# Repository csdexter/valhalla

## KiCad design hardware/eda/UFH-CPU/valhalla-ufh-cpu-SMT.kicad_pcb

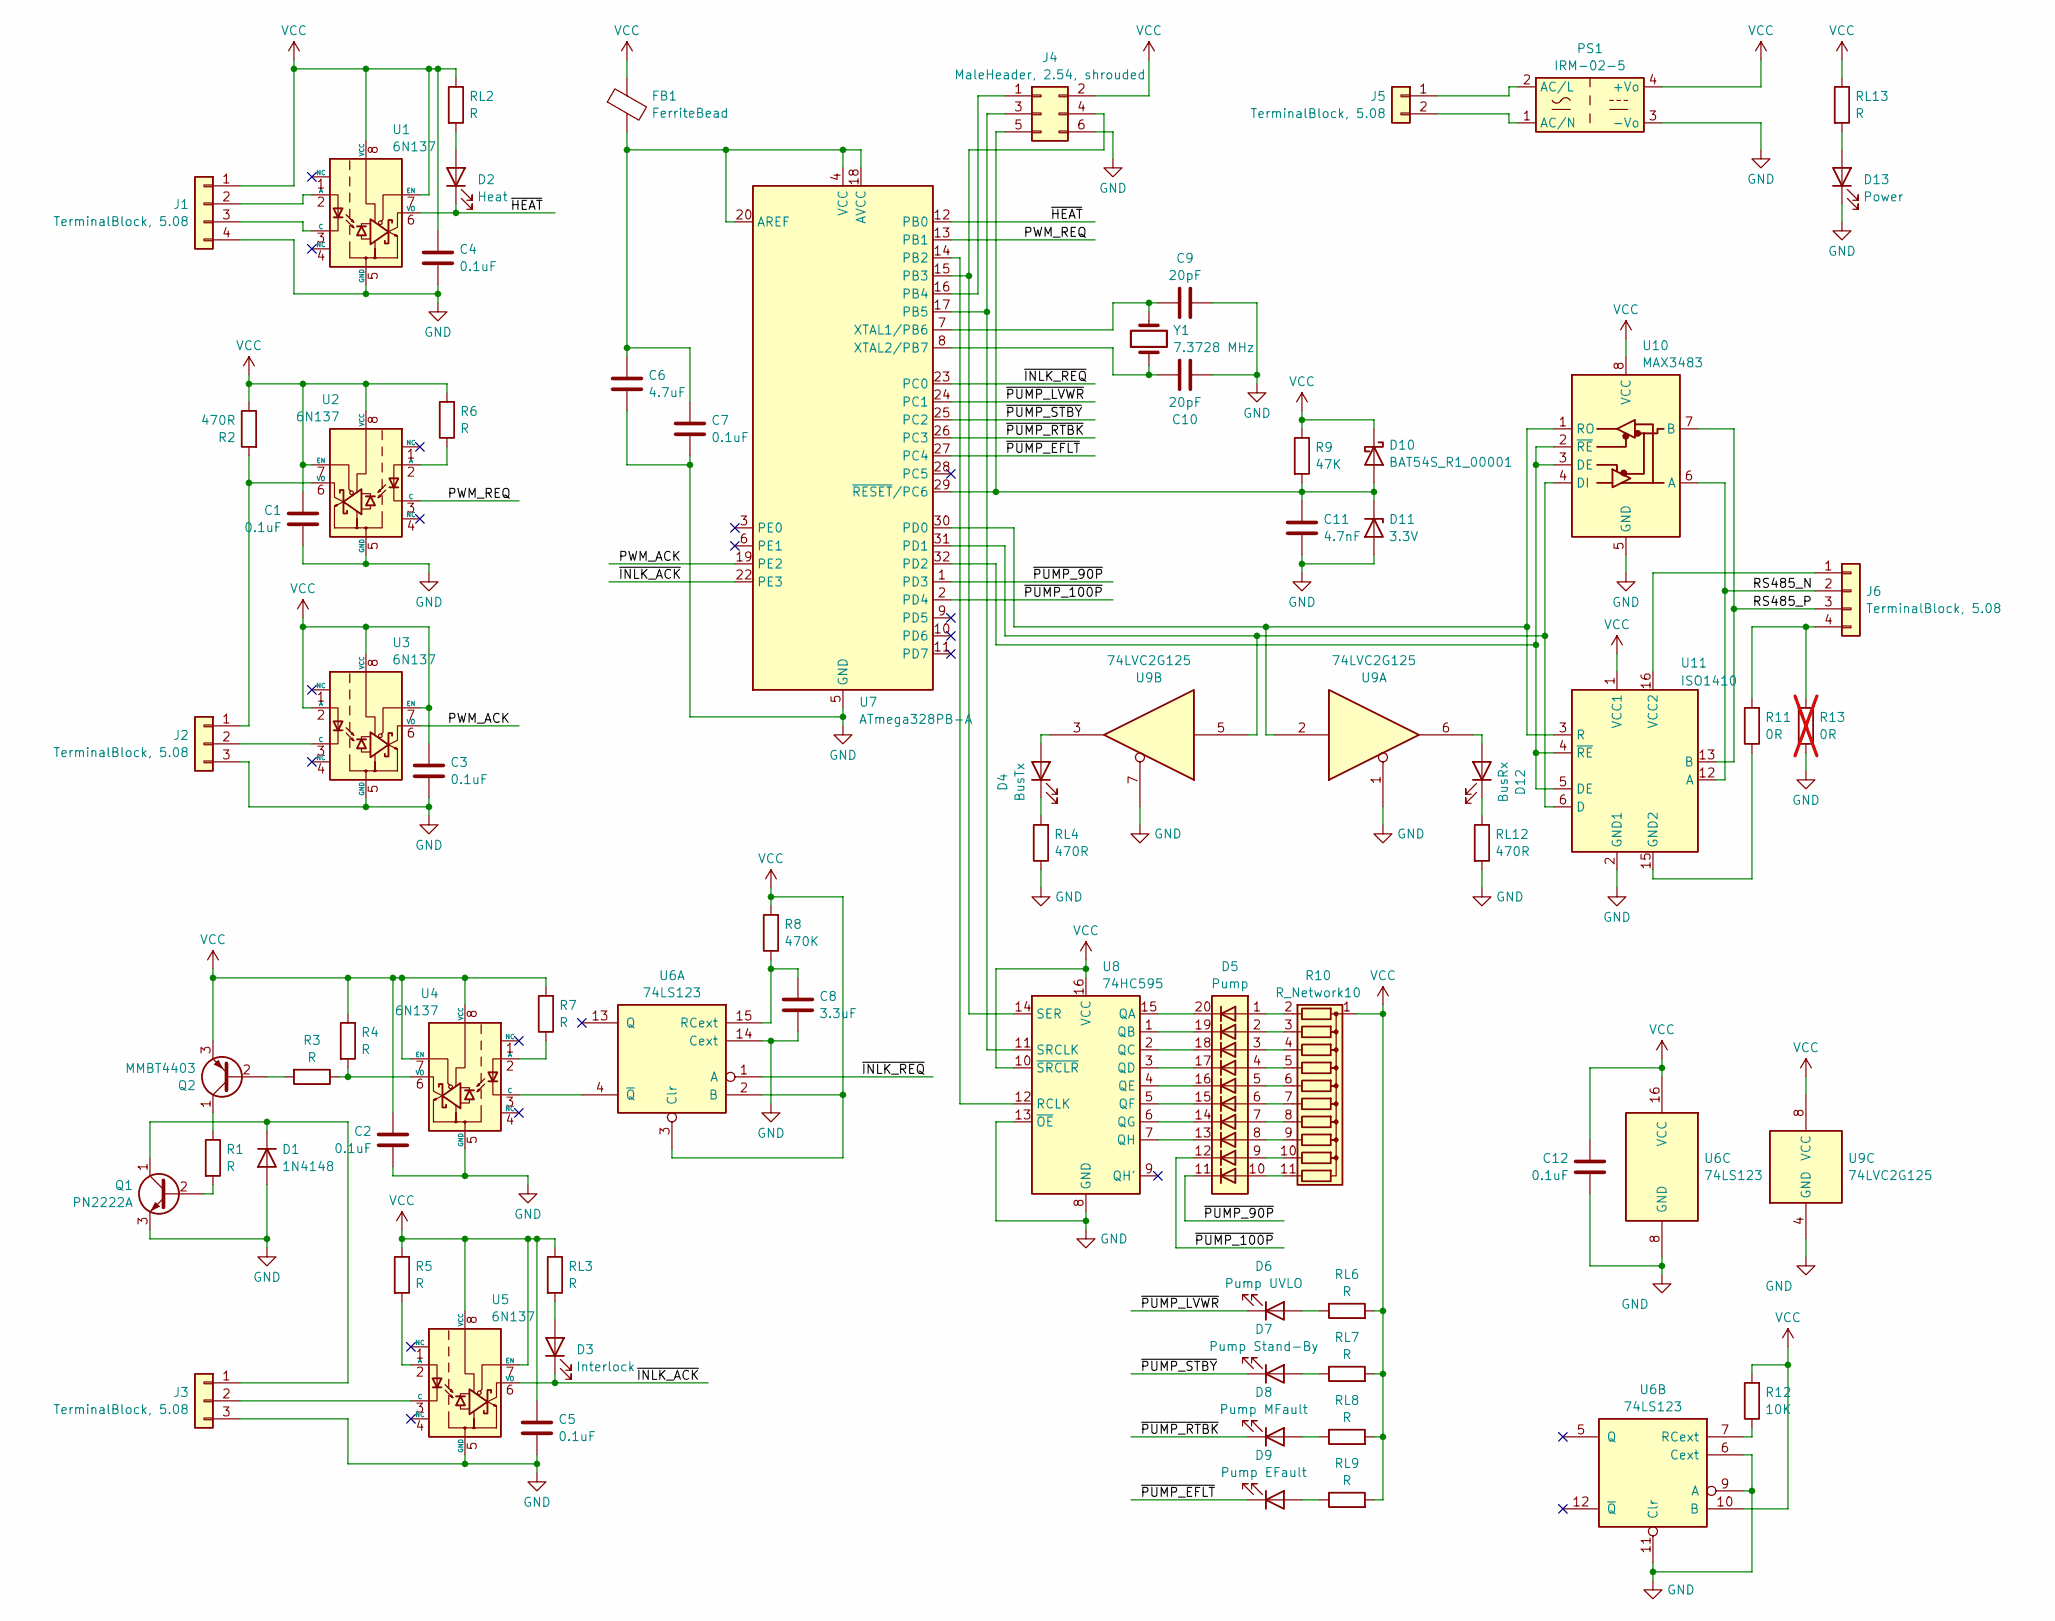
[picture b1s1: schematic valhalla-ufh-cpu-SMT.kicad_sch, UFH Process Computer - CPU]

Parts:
C1, C2, C3, C4, C5, C7, C12: 0.1uF; C_1206_3216Metric
C6: 4.7uF; C_1206_3216Metric
C8: 3.3uF; C_1206_3216Metric
C9, C10: 20pF; C_1206_3216Metric
C11: 4.7nF; C_1206_3216Metric
D1: 1N4148; D_SOD-123F
D2: Heat; LED_D5.0mm
D3: Interlock; LED_D5.0mm
D4: BusTx; LED_D5.0mm
D5: Pump; HDSP-4850
D6: Pump UVLO; LED_D5.0mm
D7: Pump Stand-By; LED_D5.0mm
D8: Pump MFault; LED_D5.0mm
D9: Pump EFault; LED_D5.0mm
D10: BAT54S_R1_00001; SOT-23-3
D11: 3.3V; SOT-23-3
D12: BusRx; LED_D5.0mm
D13: Power; LED_D5.0mm
FB1: FerriteBead; L_1206_3216Metric
J1, J6: TerminalBlock, 5.08; TerminalBlock_Phoenix_MKDS-1,5-4-5.08_1x04_P5.08mm_Horizont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
J2, J3: TerminalBlock, 5.08; TerminalBlock_Phoenix_MKDS-1,5-3-5.08_1x03_P5.08mm_Horizont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
J4: MaleHeader, 2.54, shrouded; IDC-Header_2x03_P2.54mm_Vertical
J5: TerminalBlock, 5.08; TerminalBlock_Phoenix_MKDS-1,5-2-5.08_1x02_P5.08mm_Horizont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
PS1: IRM-02-5; Converter_ACDC_MeanWell_IRM-02-xx_THT
Q1: PN2222A; TO-92_Inline_Wide
Q2: MMBT4403; SOT-23
R1, R3, R4, R5, R6, R7: R; R_1206_3216Metric
R2: 470R; R_1206_3216Metric
R8: 470K; R_1206_3216Metric
R9: 47K; R_1206_3216Metric
R10: R_Network10; R_Array_SIP11
R11: 0R; R_1206_3216Metric
R12: 10K; R_1206_3216Metric
R13: 0R; R_1206_3216Metric; not fitted
RL2, RL3, RL6, RL7, RL8, RL9, RL13: R; R_1206_3216Metric
RL4, RL12: 470R; R_1206_3216Metric
U1, U2, U3, U4, U5: 6N137; DIP-8_W7.62mm
U6: 74LS123; SOIC-16_3.9x9.9mm_P1.27mm
U7: ATmega328PB-A; TQFP-32_7x7mm_P0.8mm
U8: 74HC595; SOIC-16_3.9x9.9mm_P1.27mm
U9: 74LVC2G125; SSOP-8_2.95x2.8mm_P0.65mm
U10: MAX3483; SOIC-8_3.9x4.9mm_P1.27mm
U11: ISO1410; SOIC-16W_7.5x10.3mm_P1.27mm
Y1: 7.3728 MHz; Crystal_SMD_HC49-SD

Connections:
/PWM_ACK: U3.6 (VO), U7.19 (PE2)
/PWM_REQ: U2.3 (C), U7.13 (PB1)
/RS485_N: J6.2, U10.6 (A), U11.12 (A)
/RS485_P: J6.3, U10.7 (B), U11.13 (B)
/~HEAT: D2.1 (K), U1.6 (VO), U7.12 (PB0)
/~INLK_ACK: D3.1 (K), U5.6 (VO), U7.22 (PE3)
/~INLK_REQ: U6.1 (A), U7.23 (PC0)
/~PUMP_90P: D5.11 (K), U7.1 (PD3)
/~PUMP_100P: D5.12 (K), U7.2 (PD4)
/~PUMP_EFLT: D9.1 (K), U7.27 (PC4)
/~PUMP_LVWR: D6.1 (K), U7.24 (PC1)
/~PUMP_RTBK: D8.1 (K), U7.26 (PC3)
/~PUMP_STBY: D7.1 (K), U7.25 (PC2)
GND: C1.2, C2.2, C3.2, C4.2, C5.2, C6.2, C7.2, C8.1, C9.2, C10.2, C11.2, C12.1, D1.2 (A), D11.2 (A), D13.1 (K), J1.4, J2.3, J3.3, J4.6, PS1.3 (-Vo), Q1.3 (E), R13.1, RL4.1, RL12.2, U1.5 (GND), U2.5 (GND), U3.5 (GND), U4.5 (GND), U5.5 (GND), U6.6 (Cext), U6.8 (GND), U6.9 (A), U6.11 (Clr), U6.14 (Cext), U7.5 (GND), U7.21 (GND), U8.8 (GND), U8.13 (~OE), U9.1, U9.4 (GND), U9.7, U10.5 (GND), U11.2 (GND1), U11.8 (GND1)
unnamed: D1.1 (K), J3.1, Q1.1 (C)
unnamed: D2.2 (A), RL2.2
unnamed: D3.2 (A), RL3.2
unnamed: D4.2 (A), U9.3
unnamed: D4.1 (K), RL4.2
unnamed: D6.2 (A), RL6.1
unnamed: D7.2 (A), RL7.1
unnamed: D8.2 (A), RL8.1
unnamed: D9.2 (A), RL9.1
unnamed: C11.1, D10.2 (A), D11.1 (K), J4.5, R9.2, U7.29 (~RESET/PC6)
unnamed: D12.2 (A), U9.6
unnamed: D12.1 (K), RL12.1
unnamed: D13.2 (A), RL13.2
unnamed: J1.2, U1.2 (A)
unnamed: J1.3, U1.3 (C)
unnamed: J2.1, R2.2, U2.6 (VO)
unnamed: J2.2, U3.3 (C)
unnamed: J3.2, U5.3 (C)
unnamed: J4.1, U7.16 (PB4)
unnamed: J4.3, U7.17 (PB5), U8.11 (SRCLK)
unnamed: J4.4, U7.15 (PB3), U8.14 (SER)
unnamed: J5.1, PS1.2 (AC/L)
unnamed: J5.2, PS1.1 (AC/N)
unnamed: J6.1, U11.16 (VCC2)
unnamed: J6.4, R11.2, R13.2
unnamed: Q1.2 (B), R1.2
unnamed: Q2.2 (B), R3.2
unnamed: Q2.1 (C), R1.1
unnamed: D5.1 (A), R10.2 (R1)
unnamed: D5.2 (A), R10.3 (R2)
unnamed: D5.3 (A), R10.4 (R3)
unnamed: D5.4 (A), R10.5 (R4)
unnamed: D5.5 (A), R10.6 (R5)
unnamed: D5.6 (A), R10.7 (R6)
unnamed: D5.7 (A), R10.8 (R7)
unnamed: D5.8 (A), R10.9 (R8)
unnamed: D5.9 (A), R10.10 (R9)
unnamed: D5.10 (A), R10.11 (R10)
unnamed: R11.1, U11.9 (GND2), U11.15 (GND2)
unnamed: R6.1, U2.2 (A)
unnamed: R7.1, U4.2 (A)
unnamed: U4.3 (C), U6.4 (~Q)
unnamed: R3.1, R4.2, U4.6 (VO)
unnamed: R5.2, U5.2 (A)
unnamed: C8.2, R8.1, U6.15 (RCext)
unnamed: R12.1, U6.7 (RCext)
unnamed: C6.1, C7.1, FB1.2, U7.4 (VCC), U7.18 (AVCC), U7.20 (AREF)
unnamed: U7.14 (PB2), U8.12 (RCLK)
unnamed: C9.1, U7.7 (XTAL1/PB6), Y1.2
unnamed: C10.1, U7.8 (XTAL2/PB7), Y1.1
unnamed: D5.20 (K), U8.15 (QA)
unnamed: D5.19 (K), U8.1 (QB)
unnamed: D5.18 (K), U8.2 (QC)
unnamed: D5.17 (K), U8.3 (QD)
unnamed: D5.16 (K), U8.4 (QE)
unnamed: D5.15 (K), U8.5 (QF)
unnamed: D5.14 (K), U8.6 (QG)
unnamed: D5.13 (K), U8.7 (QH)
unnamed: U7.32 (PD2), U10.2 (~RE), U10.3 (DE), U11.4 (~RE), U11.5 (DE)
unnamed: U7.31 (PD1), U9.5, U10.4 (DI), U11.6 (D)
unnamed: U7.30 (PD0), U9.2, U10.1 (RO), U11.3 (R)
VCC: C1.1, C2.1, C3.1, C4.1, C5.1, C12.2, D10.1 (K), FB1.1, J1.1, J4.2, PS1.4 (+Vo), Q2.3 (E), R2.1, R4.1, R5.1, R6.2, R7.2, R8.2, R9.1, R10.1 (common), R12.2, RL2.1, RL3.1, RL6.2, RL7.2, RL8.2, RL9.2, RL13.1, U1.7 (EN), U1.8 (VCC), U2.7 (EN), U2.8 (VCC), U3.2 (A), U3.7 (EN), U3.8 (VCC), U4.7 (EN), U4.8 (VCC), U5.7 (EN), U5.8 (VCC), U6.2 (B), U6.3 (Clr), U6.10 (B), U6.16 (VCC), U8.10 (~SRCLR), U8.16 (VCC), U9.8 (VCC), U10.8 (VCC), U11.1 (VCC1)

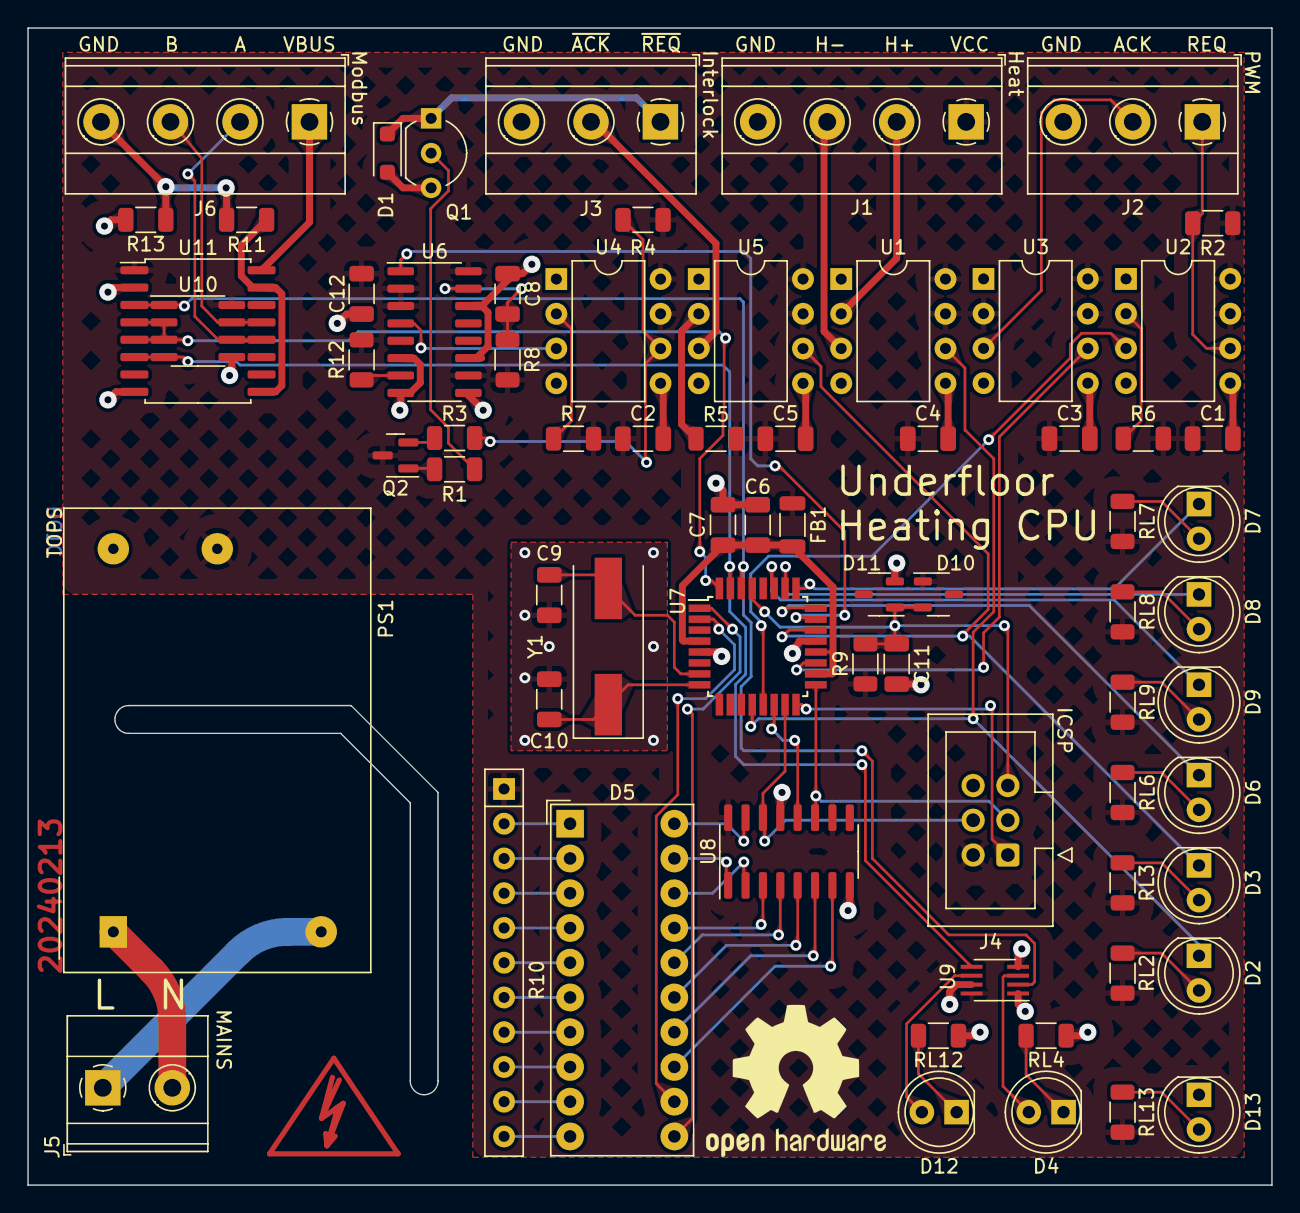
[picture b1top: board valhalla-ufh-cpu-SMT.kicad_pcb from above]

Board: 2 copper layers, 90.9 x 84.6 mm, 69 parts (0 on the bottom side), 76 nets.

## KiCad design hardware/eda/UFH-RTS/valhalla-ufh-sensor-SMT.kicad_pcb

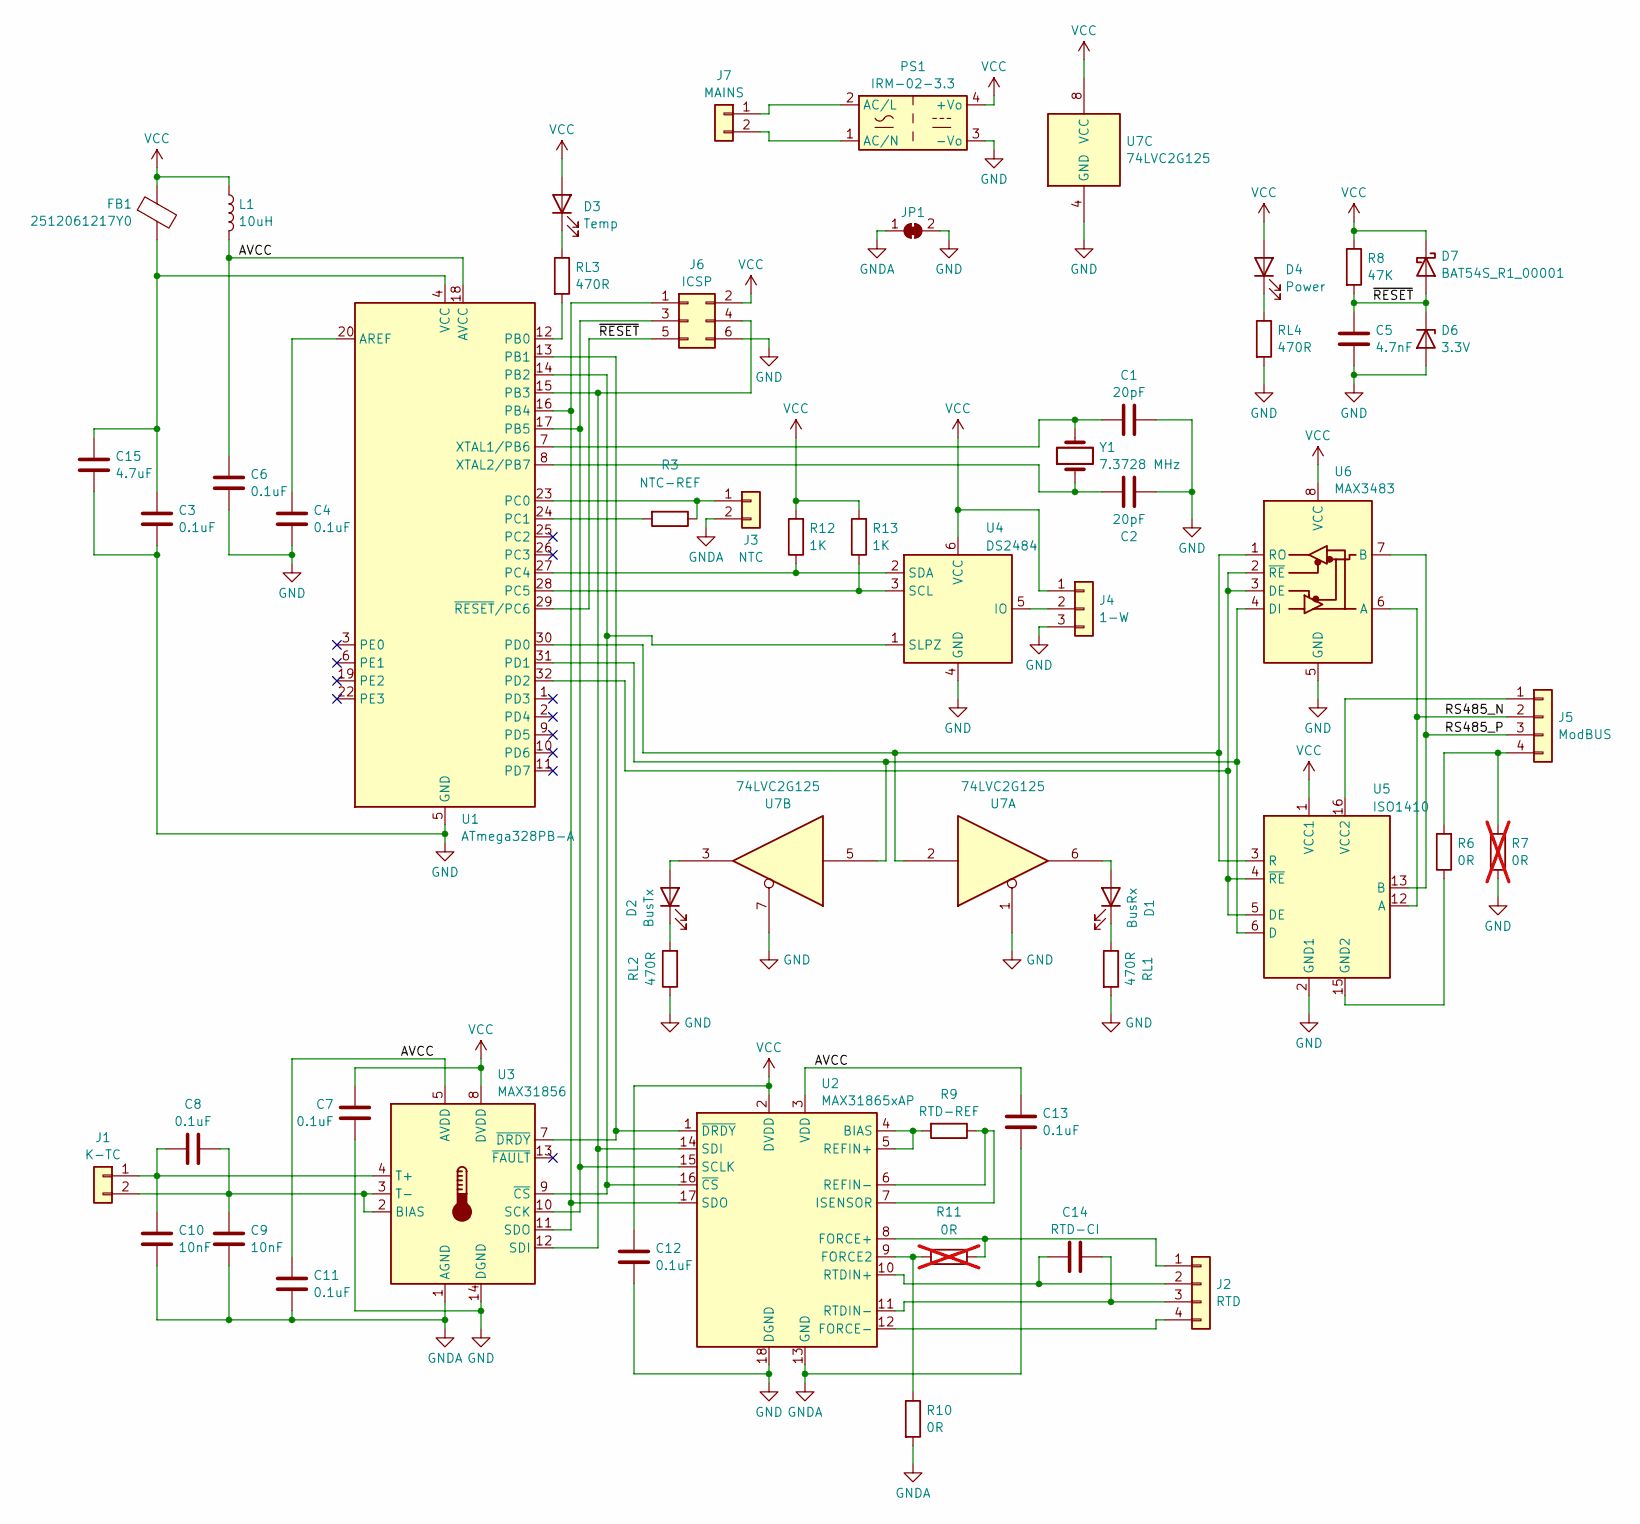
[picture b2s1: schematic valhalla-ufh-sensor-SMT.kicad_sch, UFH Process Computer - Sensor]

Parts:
C1, C2: 20pF; C_1206_3216Metric
C3, C4, C6, C7, C8, C11, C12, C13: 0.1uF; C_1206_3216Metric
C5: 4.7nF; C_1206_3216Metric
C9, C10: 10nF; C_1206_3216Metric
C14: RTD-CI; C_1206_3216Metric
C15: 4.7uF; C_1206_3216Metric
D1: BusRx; LED_D5.0mm
D2: BusTx; LED_D5.0mm
D3: Temp; LED_D5.0mm
D4: Power; LED_D5.0mm
D6: 3.3V; SOT-23-3
D7: BAT54S_R1_00001; SOT-23-3
FB1: 2512061217Y0; L_1206_3216Metric
J1: K-TC; TerminalBlock_Phoenix_MKDS-1,5-2-5.08_1x02_P5.08mm_Horizont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
J2: RTD; TerminalBlock_Phoenix_MKDS-1,5-4-5.08_1x04_P5.08mm_Horizont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
J3: NTC; TerminalBlock_Phoenix_MKDS-1,5-2-5.08_1x02_P5.08mm_Horizont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
J4: 1-W; TerminalBlock_Phoenix_MKDS-1,5-3-5.08_1x03_P5.08mm_Horizont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
J5: ModBUS; TerminalBlock_Phoenix_MKDS-1,5-4-5.08_1x04_P5.08mm_Horizont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
J6: ICSP; IDC-Header_2x03_P2.54mm_Vertical
J7: MAINS; TerminalBlock_Phoenix_MKDS-1,5-2-5.08_1x02_P5.08mm_Horizont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
JP1: SolderJumper-2_P1.3mm_Bridged2Bar_Pad1.0x1.5mm
L1: 10uH; L_1210_3225Metric
PS1: IRM-02-3.3; Converter_ACDC_MeanWell_IRM-02-xx_THT
R3: NTC-REF; R_1206_3216Metric
R6, R10: 0R; R_1206_3216Metric
R7, R11: 0R; R_1206_3216Metric; not fitted
R8: 47K; R_1206_3216Metric
R9: RTD-REF; R_1206_3216Metric
R12, R13: 1K; R_1206_3216Metric
RL1, RL2, RL3, RL4: 470R; R_1206_3216Metric
U1: ATmega328PB-A; TQFP-32_7x7mm_P0.8mm
U2: MAX31865xAP; SSOP-20_5.3x7.2mm_P0.65mm
U3: MAX31856; TSSOP-14_4.4x5mm_P0.65mm
U4: DS2484; SOT-23-6
U5: ISO1410; SOIC-16W_7.5x10.3mm_P1.27mm
U6: MAX3483; SOIC-8_3.9x4.9mm_P1.27mm
U7: 74LVC2G125; SSOP-8_2.95x2.8mm_P0.65mm
Y1: 7.3728 MHz; Crystal_SMD_HC49-SD

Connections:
/AVCC: C6.1, C11.1, C13.1, L1.2, U1.18 (AVCC), U2.3 (VDD), U3.5 (AVDD)
/RS485_N: J5.2, U5.12 (A), U6.6 (A)
/RS485_P: J5.3, U5.13 (B), U6.7 (B)
/~RESET: C5.1, D6.1 (K), D7.2 (A), J6.5, R8.2, U1.29 (~RESET/PC6)
GND: C1.2, C2.2, C3.2, C4.2, C5.2, C6.2, C7.2, C12.2, C15.2, D6.2 (A), J4.3, J6.6, JP1.2 (B), PS1.3 (-Vo), R7.1, RL1.2, RL2.1, RL4.2, U1.5 (GND), U1.21 (GND), U2.18 (DGND), U3.14 (DGND), U4.4 (GND), U5.2 (GND1), U5.8 (GND1), U6.5 (GND), U7.1, U7.4 (GND), U7.7
GNDA: C9.2, C10.2, C11.2, C13.2, J3.2, JP1.1 (A), R10.2, U2.13 (GND), U2.19 (GND), U3.1 (AGND)
unnamed: D1.2 (A), U7.6
unnamed: D1.1 (K), RL1.1
unnamed: D2.2 (A), U7.3
unnamed: D2.1 (K), RL2.2
unnamed: D3.1 (K), RL3.1
unnamed: D4.1 (K), RL4.1
unnamed: C8.1, C10.1, J1.1, U3.4 (T+)
unnamed: C8.2, C9.1, J1.2, U3.2 (BIAS), U3.3 (T-)
unnamed: J2.1, R11.2, U2.8 (FORCE+)
unnamed: C14.1, J2.2, U2.10 (RTDIN+)
unnamed: C14.2, J2.3, U2.11 (RTDIN-)
unnamed: J2.4, U2.12 (FORCE-)
unnamed: J3.1, R3.1, U1.23 (PC0)
unnamed: J4.2, U4.5 (IO)
unnamed: J5.1, U5.16 (VCC2)
unnamed: J5.4, R6.2, R7.2
unnamed: J6.1, U1.16 (PB4), U2.17 (SDO), U3.11 (SDO)
unnamed: J6.3, U1.17 (PB5), U2.15 (SCLK), U3.10 (SCK)
unnamed: J6.4, U1.15 (PB3), U2.14 (SDI), U3.12 (SDI)
unnamed: J7.1, PS1.2 (AC/L)
unnamed: J7.2, PS1.1 (AC/N)
unnamed: R6.1, U5.9 (GND2), U5.15 (GND2)
unnamed: C4.1, U1.20 (AREF)
unnamed: RL3.2, U1.12 (PB0)
unnamed: U1.13 (PB1), U2.1 (~DRDY), U3.7 (~DRDY)
unnamed: U1.14 (PB2), U2.16 (~CS), U3.9 (~CS), U4.1 (SLPZ)
unnamed: R3.2, U1.24 (PC1)
unnamed: R12.1, U1.27 (PC4), U4.2 (SDA)
unnamed: R13.1, U1.28 (PC5), U4.3 (SCL)
unnamed: U1.30 (PD0), U5.3 (R), U6.1 (RO), U7.2
unnamed: U1.31 (PD1), U5.6 (D), U6.4 (DI), U7.5
unnamed: U1.32 (PD2), U5.4 (~RE), U5.5 (DE), U6.2 (~RE), U6.3 (DE)
unnamed: C3.1, C15.1, FB1.2, U1.4 (VCC)
unnamed: C1.1, U1.7 (XTAL1/PB6), Y1.2
unnamed: C2.1, U1.8 (XTAL2/PB7), Y1.1
unnamed: R9.2, U2.4 (BIAS), U2.5 (REFIN+)
unnamed: R10.1, R11.1, U2.9 (FORCE2)
unnamed: R9.1, U2.6 (REFIN-), U2.7 (ISENSOR)
VCC: C7.1, C12.1, D3.2 (A), D4.2 (A), D7.1 (K), FB1.1, J4.1, J6.2, L1.1, PS1.4 (+Vo), R8.1, R12.2, R13.2, U2.2 (DVDD), U3.8 (DVDD), U4.6 (VCC), U5.1 (VCC1), U6.8 (VCC), U7.8 (VCC)

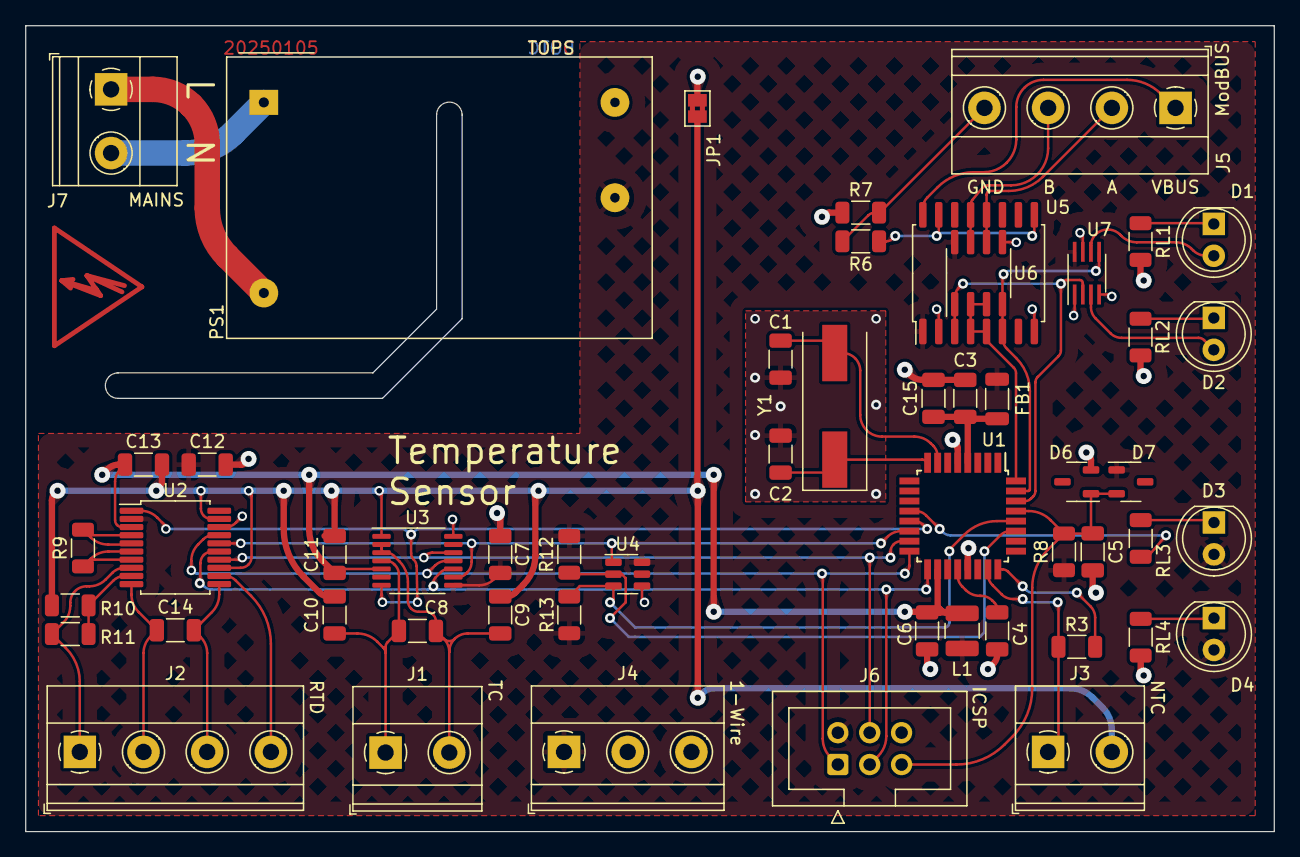
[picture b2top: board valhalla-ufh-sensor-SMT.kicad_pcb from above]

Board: 2 copper layers, 99.6 x 64.3 mm, 53 parts (0 on the bottom side), 45 nets.
